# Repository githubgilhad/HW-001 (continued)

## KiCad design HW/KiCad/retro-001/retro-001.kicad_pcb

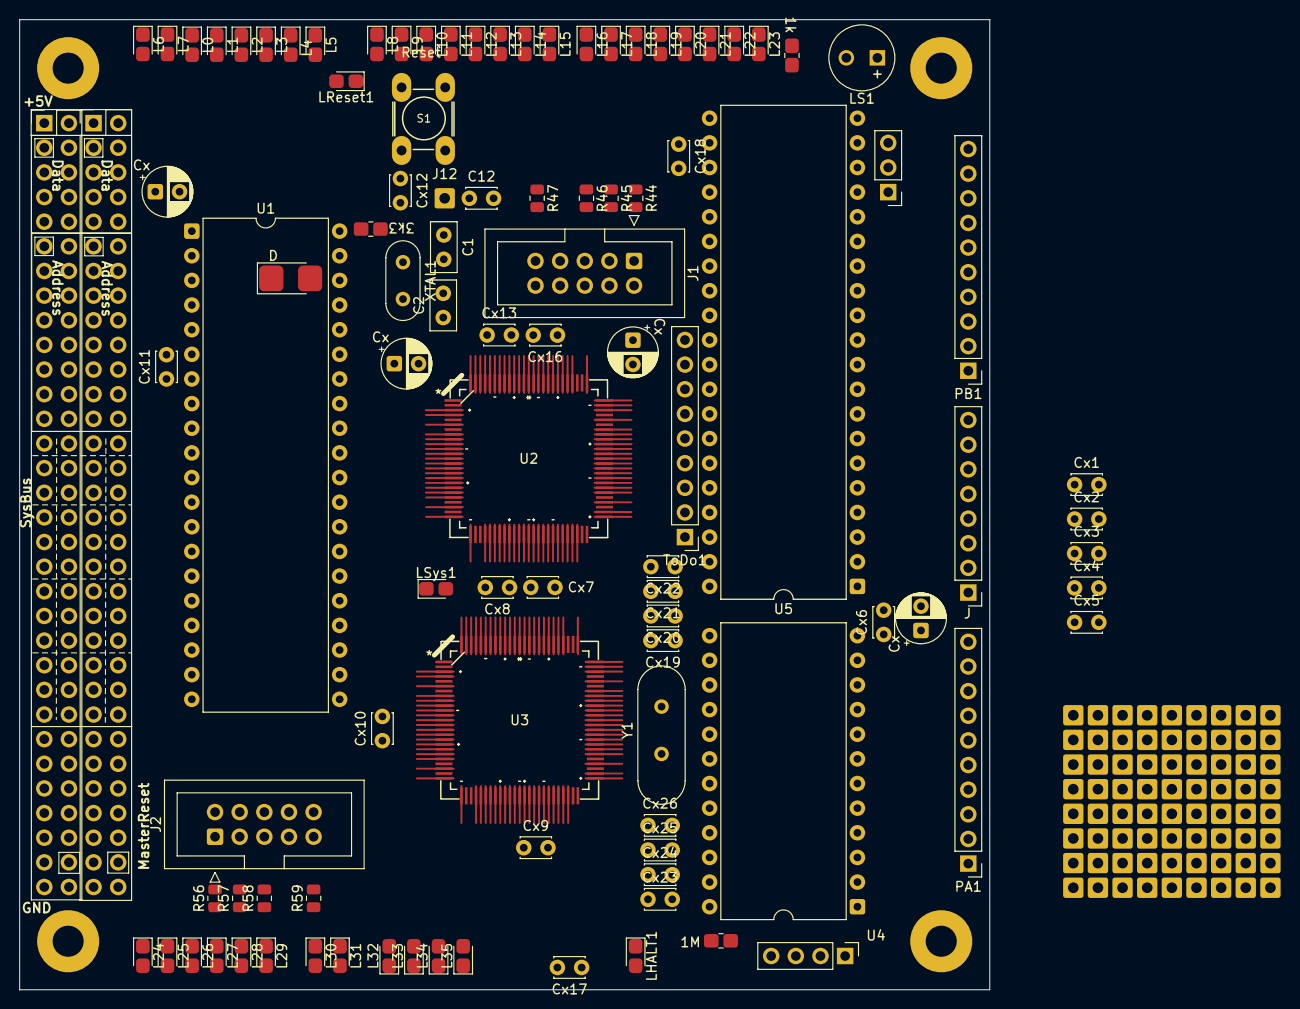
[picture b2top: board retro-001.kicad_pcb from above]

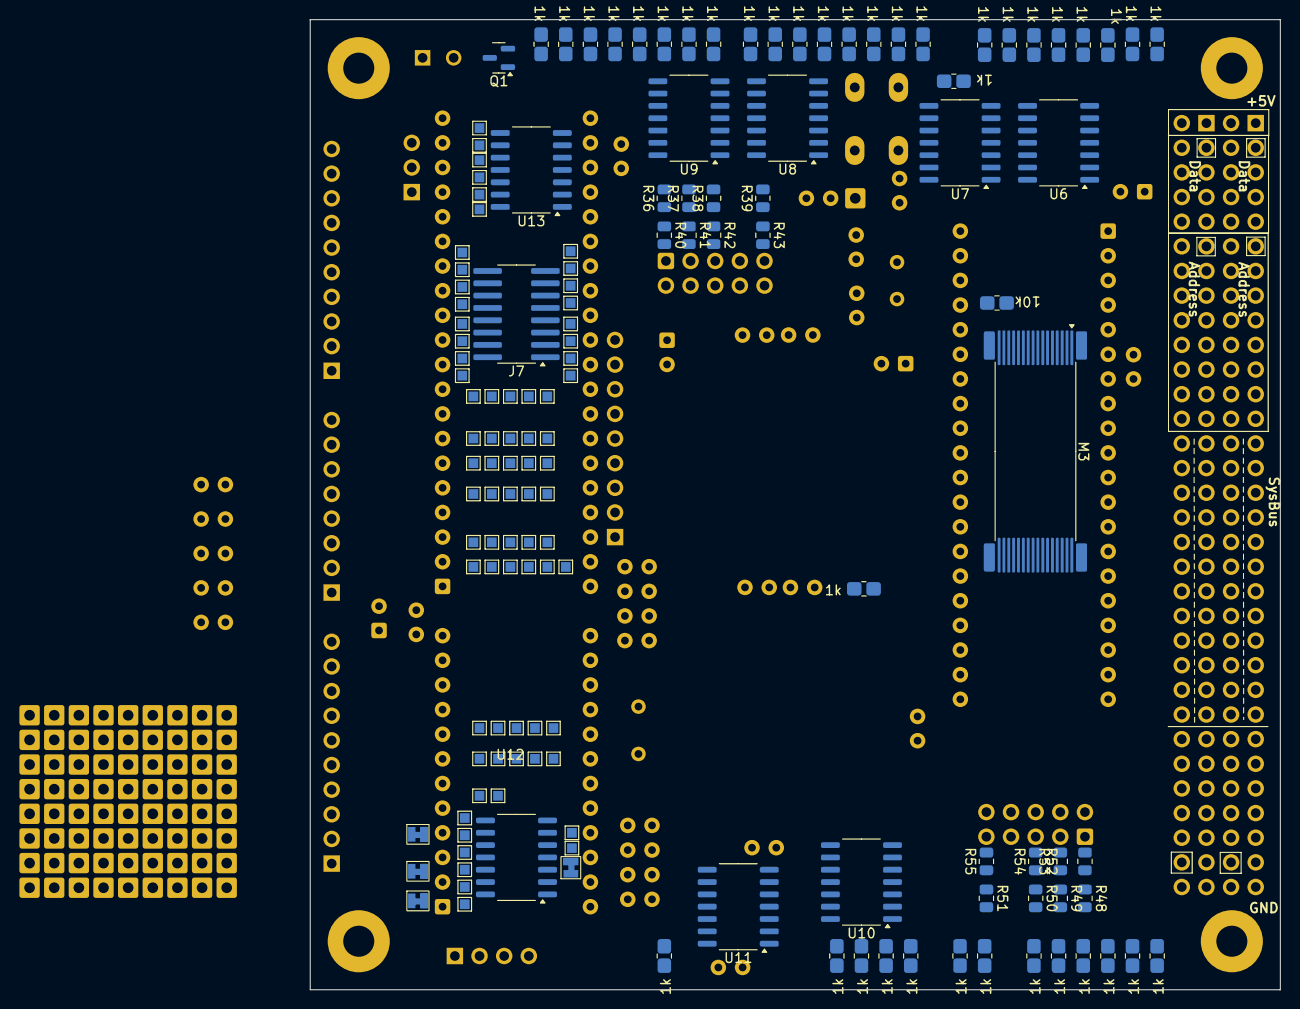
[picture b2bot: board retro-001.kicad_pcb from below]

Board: 2 copper layers, 100.0 x 100.0 mm, 322 parts (144 on the bottom side), 280 nets, no tracks yet.

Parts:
C1, C2: 20p; C_Disc_D5.0mm_W2.5mm_P2.50mm
C12: 100n RESET; C_Disc_D3.0mm_W2.0mm_P2.50mm
Cx1, Cx2, Cx3, Cx4, Cx5, Cx6, Cx7, Cx8, Cx9, Cx10, Cx11, Cx12, Cx13, Cx16, Cx17, Cx18: Cx; C_Disc_D3.0mm_W2.0mm_P2.50mm
Cx14, Cx15, Cx27, Cx28: Cx; CP_Radial_D5.0mm_P2.50mm
Cx19, Cx20, Cx21, Cx22, Cx23, Cx24, Cx25, Cx26: 10p; C_Disc_D3.0mm_W2.0mm_P2.50mm
D2: D; D_1210_3225Metric_HandSolder
H5, H6, H7, H8: MountingHole; MountingHole_3.2mm_M3_Pad
J1, J2: Conn_02x05_JTAG; IDC-Header_2x05_P2.54mm_Vertical
J3: Serial; PinHeader_1x04_P2.54mm_Vertical
J4: SysBus; PinSocket_2x32_P2.54mm_Vertical
J6: SysBus; PinHeader_2x32_P2.54mm_Vertical_down
J7: Conn_01x16_Pin; G_SOIC-16_3.9x9.9mm_HandSolder
J12: Reset; PinHole_1x01_2.54xrectangle
J21, J22, J37, J38, J39, J40, J41, J42, J43, J44, J45, J46, J47, J48, J49, J50, J51, J52, J53, J54, J55, J56, J57, J58, J59, J60, J61, J62, J63, J64, J65, J66, J67, J68, J69, J70, J71, J72, J73, J74, J75, J76, J77, J78, J79, J80, J81, J82, J83, J84, J85, J86, J87, J88, J89, J90, J91, J92, J93, J94, J95, J96, J97, J98, J99, J100, J101, J102, J103, J104, J105, J106: x; PinHole_1x01_2.54xrectangle
JP1: Nx4; SolderJumper-2_P1.3mm_Bridged_Pad1.0x1.5mm
JP2: Nx5; SolderJumper-2_P1.3mm_Bridged_Pad1.0x1.5mm
JP3: Nx6; SolderJumper-2_P1.3mm_Bridged_Pad1.0x1.5mm
JP13: Nx3; SolderJumper-2_P1.3mm_Bridged_Pad1.0x1.5mm
Jx1: BugFix; PinHeader_1x03_P2.54mm_Vertical
Jx4: J; PinHeader_1x08_P2.54mm_Vertical
L0, L1, L2, L3, L4, L5, L6, L7, L8, L9, L10, L11, L12, L13, L14, L15, L16, L17, L18, L19, L20, L21, L22, L23, L24, L25, L26, L27, L28, L29, L30, L31, L32, L33, L34, L35: A0; LED_0805_2012Metric
LHALT1: A0; LED_0805_2012Metric
LReset1: A0; LED_0805_2012Metric
LS1: Speaker_Crystal; MagneticBuzzer_Kingstate_KCG0601
LSys1: A0; LED_0805_2012Metric
M3: CY7C109D-10ZXI; G_TSOP-I-32_18.4x8mm_HandSolder
PA1: J; PinHeader_1x10_P2.54mm_Vertical
PB1: J; PinHeader_1x10_P2.54mm_Vertical
Q1: MMBT3904; SOT-23
R0, R1, R2, R3, R4, R5, R6, R7, R8, R9, R10, R11, R12, R13, R14, R15, R16, R17, R18, R19, R20, R21, R22, R23, R24, R25, R26, R27, R28, R29, R30, R31, R32, R33, R34, R35, R61, R62, R65, R66: 1k; R_0805_2012Metric_Pad1.20x1.40mm_HandSolder
R36, R37, R38, R39, R44, R45, R46, R47, R48, R49, R50, R51, R56, R57, R58, R59: 5k8; R_0805_2012Metric
R40, R41, R42, R43, R52, R53, R54, R55: 220; R_0805_2012Metric
R60: 1M; R_0805_2012Metric_Pad1.20x1.40mm_HandSolder
R63: 3k3; R_0805_2012Metric_Pad1.20x1.40mm_HandSolder
R64: 10k; R_0805_2012Metric_Pad1.20x1.40mm_HandSolder
S1: Reset; G_Arduino_switch
TP1, TP16: 7; TestPoint_Pad_1.0x1.0mm
TP2, TP9: 0; TestPoint_Pad_1.0x1.0mm
TP3, TP10: 1; TestPoint_Pad_1.0x1.0mm
TP4, TP11: 2; TestPoint_Pad_1.0x1.0mm
TP5, TP12: 3; TestPoint_Pad_1.0x1.0mm
TP6, TP13: 4; TestPoint_Pad_1.0x1.0mm
TP7, TP14: 5; TestPoint_Pad_1.0x1.0mm
TP8, TP15: 6; TestPoint_Pad_1.0x1.0mm
TP17: D; TestPoint_Pad_1.0x1.0mm
TP18: Clk; TestPoint_Pad_1.0x1.0mm
TP19: Q; TestPoint_Pad_1.0x1.0mm
TP20: ~{Q}; TestPoint_Pad_1.0x1.0mm
TP21: ~{R}; TestPoint_Pad_1.0x1.0mm
TP22: ~{S}; TestPoint_Pad_1.0x1.0mm
TP23: N3; TestPoint_Pad_1.0x1.0mm
TP24: N4; TestPoint_Pad_1.0x1.0mm
TP25: N5; TestPoint_Pad_1.0x1.0mm
TP26: N6; TestPoint_Pad_1.0x1.0mm
TP27: ~{N3}; TestPoint_Pad_1.0x1.0mm
TP28: ~{N4}; TestPoint_Pad_1.0x1.0mm
TP29: ~{N5}; TestPoint_Pad_1.0x1.0mm
TP30: ~{N6}; TestPoint_Pad_1.0x1.0mm
TP31, TP32, TP33, TP34, TP35, TP36, TP37, TP38, TP39, TP40, TP41, TP42, TP43, TP44, TP45, TP46, TP47, TP48, TP49, TP50, TP51, TP52, TP53, TP54, TP55, TP56, TP57, TP58, TP59, TP60, TP61, TP62, TP63: IO; TestPoint_Pad_1.0x1.0mm
TP65, TP66, TP67, TP68, TP69, TP70, TP71, TP72, TP73, TP74: I; TestPoint_Pad_1.0x1.0mm
ToDo1: J; PinHeader_1x09_P2.54mm_Vertical
U1: HD6309; DIP-40_W15.24mm
U2, U3: ATF1504AS-10AU100; ATF1504-AS_TQFP100_long
U4: MC68B50; DIP-24_W15.24mm
U5: 6822; DIP-40_W15.24mm
U6, U7, U8, U9, U10, U11: 74HC14; SOIC-14_3.9x8.7mm_P1.27mm
U12: 74HC04; SOIC-14_3.9x8.7mm_P1.27mm
U13: 74HC74; SOIC-14_3.9x8.7mm_P1.27mm
XTAL1: 16MHz; Crystal_HC52-6mm_Vertical
Y1: 1.8432 MHz; Crystal_THT_15_5mm

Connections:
+5V: Cx1.1, Cx2.1, Cx3.1, Cx4.1, Cx5.1, Cx6.1, Cx7.1, Cx8.1, Cx9.1, Cx10.1, Cx11.1, Cx12.1, Cx13.1, Cx14.1, Cx15.1, Cx16.1, Cx17.1, Cx18.1, Cx27.1, Cx28.1, D2.1 (K), J1.4 (Vcc), J2.4 (Vcc), J3.4, J4.1, J4.2, J6.1, J6.2, Jx4.8, L0.2 (A), L1.2 (A), L2.2 (A), L3.2 (A), L4.2 (A), L5.2 (A), L6.2 (A), L7.2 (A), L8.2 (A), L9.2 (A), L10.2 (A), L11.2 (A), L12.2 (A), L13.2 (A), L14.2 (A), L15.2 (A), L16.2 (A), L17.2 (A), L18.2 (A), L19.2 (A), L20.2 (A), L21.2 (A), L22.2 (A), L23.2 (A), L32.2 (A), L33.2 (A), L34.2 (A), L35.2 (A), LS1.1, M3.6 (CS2/CE2), M3.8 (VCC), PA1.10, PB1.10, R36.2, R37.2, R38.2, R39.2, R48.2, R49.2, R50.2, R51.2, R62.2, R63.1, R64.1, R65.2, R66.2, U1.7 (VCC), U2.3 (VCCIO), U2.18 (VCCIO), U2.34 (VCCIO), U2.39 (VCCINT), U2.51 (VCCIO), U2.66 (VCCIO), U2.82 (VCCIO), U2.91 (VCCINT), U3.3 (VCCIO), U3.18 (VCCIO), U3.34 (VCCIO), U3.39 (VCCINT), U3.51 (VCCIO), U3.66 (VCCIO), U3.82 (VCCIO), U3.91 (VCCINT), U4.8 (CS0), U4.10 (CS1), U4.12 (VCC), U5.20 (VCC), U5.22 (CS0), U5.24 (CS1), U6.14 (VCC), U7.14 (VCC), U8.14 (VCC), U9.14 (VCC), U10.14 (VCC), U11.14 (VCC), U12.14 (VCC), U13.1 (~R), U13.4 (~S), U13.14 (VCC)
/A12: J4.23, J6.23, M3.12 (A12), U3.100 (I/O)
/A13: J4.24, J6.24, M3.4 (A13), U3.99 (I/O)
/A14: J4.25, J6.25, M3.11 (A14), U3.98 (I/O)
/A15: J4.26, J6.26, M3.7 (A15), U3.97 (I/O)
/CA0: J4.11, J6.11, M3.20 (A0), U1.8 (A0), U2.6 (I/O), U4.11 (RS), U5.36 (RS0), U7.5
/CA1: J4.12, J6.12, M3.19 (A1), U1.9 (A1), U2.8 (I/O), U5.35 (RS1), U7.9
/CA2: J4.13, J6.13, M3.18 (A2), U1.10 (A2), U2.9 (I/O), U7.11
/CA3: J4.14, J6.14, M3.17 (A3), U1.11 (A3), U2.10 (I/O), U7.13
/CA4: J4.15, J6.15, M3.16 (A4), U1.12 (A4), U2.12 (I/O/PD1), U8.1
/CA5: J4.16, J6.16, M3.15 (A5), U1.13 (A5), U2.13 (I/O), U8.3
/CA6: J4.17, J6.17, M3.14 (A6), U1.14 (A6), U2.14 (I/O), U8.5
/CA7: J4.18, J6.18, M3.13 (A7), U1.15 (A7), U2.16 (I/O), U8.9
/CA8: J4.19, J6.19, M3.3 (A8), U1.16 (A8), U2.17 (I/O), U8.11
/CA9: J4.20, J6.20, M3.2 (A9), U1.17 (A9), U2.19 (I/O), U8.13
/CA10: J4.21, J6.21, M3.31 (A10), U1.18 (A10), U2.20 (I/O), U9.1
/CA11: J4.22, J6.22, M3.1 (A11), U1.19 (A11), U2.21 (I/O), U9.3
/E: J4.61, J6.61, U1.34 (E), U2.31 (I/O), U3.17 (I/O), U4.14 (E), U5.25 (ENABLE), U13.3 (C)
/Rx: J3.1, U4.2 (Rx_Data)
/Tx: J3.2, U4.6 (Tx_Data)
/mA_16: J4.27, J6.27, U3.69 (I/O)
/mA_HALT: J4.29, J6.29, U3.68 (I/O)
/mA_READ: J4.31, J6.31, U3.67 (I/O)
/mA_SHARE_DIRTY: J4.33, J6.33, U3.65 (I/O)
/mA_SHARE_GRANTED: J4.35, J6.35, U3.64 (I/O)
/mA_SHARE_REQUEST: J4.37, J6.37, U3.63 (I/O)
/mA_SHARE_SELECT: J4.51, J6.51, U3.52 (I/O)
/mB_16: J4.28, J6.28, U3.32 (I/O)
/mB_HALT: J4.30, J6.30, U3.33 (I/O)
/mB_READ: J4.32, J6.32, U3.35 (I/O)
/mB_SHARE_DIRTY: J4.34, J6.34, U3.36 (I/O)
/mB_SHARE_GRANTED: J4.36, J6.36, U3.37 (I/O)
/mB_SHARE_REQUEST: J4.38, J6.38, U3.40 (I/O)
/mB_SHARE_SELECT: J4.52, J6.52, U3.48 (I/O)
/vCA1: Jx4.1, U5.40 (CA1)
/vCA2: Jx4.2, U5.39 (CA2)
/vCB1: Jx1.1, Jx4.3, U13.2 (D)
/vCB2: Jx4.4, U5.19 (CB2)
/v~IRQA: Jx4.5, U5.38 (~IRQA)
/v~IRQB: Jx4.6, U5.37 (~IRQB)
/~Dev_Sel_3: J4.58, J6.58, U2.83 (I/O), U10.9
/~Dev_Sel_4: J4.59, J6.59, U2.81 (I/O), U10.11
/~Dev_Sel_5: J4.60, J6.60, U2.80 (I/O), U10.13
/~FIRQ: J4.57, J6.57, U1.4 (~FIRQ)
/~IRQ: J4.56, J6.56, U1.3 (~IRQ), U4.7 (~IRQ)
/~NMI: J4.55, J6.55, U1.2 (~NMI)
/~Read: J4.54, J6.54, M3.32 (~OE), U2.96 (I/O), U11.1
/~Write: J4.53, J6.53, M3.5 (~WE), U2.94 (I/O), U11.3
ACIA Clk 1.8432 MHz: U4.3 (Rx_CLK), U4.4 (Tx_CLK), U12.4
A_G_A_DIR: J4.47, J6.47, U3.56 (I/O)
A_G_D_DIR: J4.49, J6.49, U3.54 (I/O)
A_G_ENABLE: J4.45, J6.45, U3.57 (I/O)
A_S_READ: J4.41, J6.41, U3.60 (I/O)
A_S_SELECT: J4.39, J6.39, U3.61 (I/O)
A_S_WRITE: J4.43, J6.43, U3.58 (I/O)
BA: ToDo1.6, U1.6 (BA)
BS: ToDo1.5, U1.5 (BS)
B_G_A_DIR: J4.48, J6.48, U3.46 (I/O)
B_G_D_DIR: J4.50, J6.50, U3.47 (I/O)
B_G_ENABLE: J4.46, J6.46, U3.45 (I/O)
B_S_READ: J4.42, J6.42, U3.42 (I/O/PD2)
B_S_SELECT: J4.40, J6.40, U3.41 (I/O)
B_S_WRITE: J4.44, J6.44, U3.44 (I/O)
CA12: U1.20 (A12), U2.23 (I/O), U3.23 (I/O), U9.5
CA13: U1.21 (A13), U2.25 (I/O), U3.25 (I/O), U9.9
CA14: U1.22 (A14), U2.29 (I/O), U3.29 (I/O), U9.11
CA15: U1.23 (A15), U2.30 (I/O), U3.30 (I/O), U9.13
D0: J4.3, J6.3, M3.21 (DQ0), U1.31 (D0), U3.6 (I/O), U4.22 (D0), U5.33 (D0), U7.1
D1: J4.4, J6.4, M3.22 (DQ1), U1.30 (D1), U3.8 (I/O), U4.21 (D1), U5.32 (D1), U7.3
D2: J4.5, J6.5, M3.23 (DQ2), U1.29 (D2), U3.9 (I/O), U4.20 (D2), U5.31 (D2), U6.1
D3: J4.6, J6.6, M3.25 (DQ3), U1.28 (D3), U3.10 (I/O), U4.19 (D3), U5.30 (D3), U6.3
D4: J4.7, J6.7, M3.26 (DQ4), U1.27 (D4), U3.12 (I/O/PD1), U4.18 (D4), U5.29 (D4), U6.5
D5: J4.8, J6.8, M3.27 (DQ5), U1.26 (D5), U3.13 (I/O), U4.17 (D5), U5.28 (D5), U6.9
D6: J4.9, J6.9, M3.28 (DQ6), U1.25 (D6), U3.14 (I/O), U4.16 (D6), U5.27 (D6), U6.11
D7: J4.10, J6.10, M3.29 (DQ7), U1.24 (D7), U3.16 (I/O), U4.15 (D7), U5.26 (D7), U6.13
GA16: M3.10 (A16), U3.96 (I/O)
GND: C1.1, C2.1, C12.2, Cx1.2, Cx2.2, Cx3.2, Cx4.2, Cx5.2, Cx6.2, Cx7.2, Cx8.2, Cx9.2, Cx10.2, Cx11.2, Cx12.2, Cx13.2, Cx14.2, Cx15.2, Cx16.2, Cx17.2, Cx18.2, Cx19.2, Cx20.2, Cx21.2, Cx22.2, Cx23.2, Cx24.2, Cx25.2, Cx26.2, Cx27.2, Cx28.2, J1.2 (GND), J1.10 (GND), J2.2 (GND), J2.10 (GND), J3.3, J4.63, J4.64, J6.63, J6.64, JP1.1 (A), JP2.1 (A), JP3.1 (A), JP13.1 (A), Jx4.7, L24.1 (K), L25.1 (K), L26.1 (K), L27.1 (K), L28.1 (K), L29.1 (K), L30.1 (K), L31.1 (K), LSys1.1 (K), M3.24 (GND), PA1.9, PB1.9, Q1.2 (E), R44.1, R45.1, R46.1, R47.1, R56.1, R57.1, R58.1, R59.1, S1.3 (K), S1.4 (A), ToDo1.9, U1.1 (VSS), U2.11 (GND), U2.26 (GND), U2.38 (GND), U2.43 (GND), U2.59 (GND), U2.74 (GND), U2.86 (GND), U2.95 (GND), U3.11 (GND), U3.26 (GND), U3.38 (GND), U3.43 (GND), U3.59 (GND), U3.74 (GND), U3.86 (GND), U3.95 (GND), U4.1 (VSS), U4.23 (~DCD), U4.24 (~CTS), U5.1 (VSS), U6.7 (GND), U7.7 (GND), U8.7 (GND), U9.7 (GND), U10.7 (GND), U11.7 (GND), U12.7 (GND), U13.7 (GND)
JT2_TCK: R48.1, R52.1, R56.2, U3.62 (I/O/TCK)
JT2_TDI: R51.1, R55.1, R59.2, U3.4 (I/O/TDI)
JT2_TDO: R49.1, R53.1, R57.2, U3.73 (I/O/TDO)
JT2_TMS: R50.1, R54.1, R58.2, U3.15 (I/O/TMS)
JT_TCK: R36.1, R40.1, R44.2, U2.62 (I/O/TCK)
JT_TDI: R39.1, R43.1, R47.2, U2.4 (I/O/TDI)
JT_TDO: R37.1, R41.1, R45.2, U2.73 (I/O/TDO)
JT_TMS: R38.1, R42.1, R46.2, U2.15 (I/O/TMS)
MR0: U2.100 (I/O), U3.94 (I/O), U11.5
MR1: U2.99 (I/O), U3.93 (I/O), U11.9
MR2: U2.98 (I/O), U3.92 (I/O), U11.11
MR3: U2.97 (I/O), U3.84 (I/O), U11.13
MRDY: ToDo1.7, U1.36 (MRDY)
MasterReset: C12.1, D2.2 (A), J4.62, J6.62, J12.1, LReset1.1 (K), R64.2, S1.1, S1.2, U1.37 (~RESET), U2.33 (I/O), U3.20 (I/O), U5.34 (~RESET)
unnamed: Cx19.1, Cx20.1, Cx21.1, Cx22.1, R60.1, U12.2, U12.3, Y1.2
unnamed: Cx23.1, Cx24.1, Cx25.1, Cx26.1, R60.2, U12.1, Y1.1
unnamed: J1.1 (TCK), R40.2
unnamed: J1.9 (TDI), R43.2
unnamed: J1.3 (TDO), R41.2
unnamed: J1.5 (TMS), R42.2
unnamed: J2.1 (TCK), R52.2
unnamed: J2.9 (TDI), R55.2
unnamed: J2.3 (TDO), R53.2
unnamed: J2.5 (TMS), R54.2
unnamed: J7.1, TP2.1
unnamed: J7.2, TP3.1
unnamed: J7.3, TP4.1
unnamed: J7.4, TP5.1
unnamed: J7.5, TP6.1
unnamed: J7.6, TP7.1
unnamed: J7.7, TP8.1
unnamed: J7.8, TP1.1
unnamed: J7.9, TP16.1
unnamed: J7.10, TP15.1
unnamed: J7.11, TP14.1
unnamed: J7.12, TP13.1
unnamed: J7.13, TP12.1
unnamed: J7.14, TP11.1
unnamed: J7.15, TP10.1
unnamed: J7.16, TP9.1
unnamed: JP1.2 (B), TP24.1, U12.9
unnamed: JP2.2 (B), TP25.1, U12.11
unnamed: JP3.2 (B), TP26.1, U12.13
unnamed: JP13.2 (B), TP23.1, U12.5
unnamed: Jx1.2, U5.18 (CB1)
unnamed: Jx1.3, U13.5 (Q)
unnamed: L0.1 (K), R0.1
unnamed: L1.1 (K), R1.1
unnamed: L2.1 (K), R2.1
unnamed: L3.1 (K), R3.1
unnamed: L4.1 (K), R4.1
unnamed: L5.1 (K), R5.1
unnamed: L6.1 (K), R6.1
unnamed: L7.1 (K), R7.1
unnamed: L8.1 (K), R8.1
unnamed: L9.1 (K), R9.1
unnamed: L10.1 (K), R10.1
unnamed: L11.1 (K), R11.1
unnamed: L12.1 (K), R12.1
unnamed: L13.1 (K), R13.1
unnamed: L14.1 (K), R14.1
unnamed: L15.1 (K), R15.1
unnamed: L16.1 (K), R16.1
unnamed: L17.1 (K), R17.1
unnamed: L18.1 (K), R18.1
unnamed: L19.1 (K), R19.1
unnamed: L20.1 (K), R20.1
unnamed: L21.1 (K), R21.1
unnamed: L22.1 (K), R22.1
unnamed: L23.1 (K), R23.1
unnamed: L24.2 (A), R24.1
unnamed: L25.2 (A), R25.1
unnamed: L26.2 (A), R26.1
unnamed: L27.2 (A), R27.1
unnamed: L28.2 (A), R28.1
unnamed: L29.2 (A), R29.1
unnamed: L30.2 (A), R30.1
unnamed: L31.2 (A), R31.1
unnamed: L32.1 (K), R32.1
unnamed: L33.1 (K), R33.1
unnamed: L34.1 (K), R34.1
unnamed: L35.1 (K), R35.1
unnamed: LHALT1.2 (A), R65.1
unnamed: LReset1.2 (A), R66.1
unnamed: LSys1.2 (A), R62.1
unnamed: PA1.1, U5.2 (PA0)
unnamed: PA1.2, U5.3 (PA1)
unnamed: PA1.3, U5.4 (PA2)
unnamed: PA1.4, U5.5 (PA3)
unnamed: PA1.5, U5.6 (PA4)
unnamed: PA1.6, U5.7 (PA5)
unnamed: PA1.7, U5.8 (PA6)
unnamed: PA1.8, U5.9 (PA7)
unnamed: PB1.1, U5.10 (PB0)
unnamed: PB1.2, U5.11 (PB1)
unnamed: PB1.3, U5.12 (PB2)
unnamed: PB1.4, U5.13 (PB3)
unnamed: PB1.5, U5.14 (PB4)
unnamed: PB1.6, U5.15 (PB5)
unnamed: PB1.7, U5.16 (PB6)
unnamed: PB1.8, R61.1, U5.17 (PB7)
unnamed: Q1.1 (B), R61.2
unnamed: LS1.2, Q1.3 (C)
unnamed: R0.2, U6.2
unnamed: R1.2, U6.4
unnamed: R2.2, U6.6
unnamed: R3.2, U6.8
unnamed: R4.2, U6.10
unnamed: R5.2, U6.12
unnamed: R6.2, U7.2
unnamed: R7.2, U7.4
unnamed: R8.2, U7.6
unnamed: R9.2, U7.8
unnamed: R10.2, U7.10
unnamed: R11.2, U7.12
unnamed: R12.2, U8.2
unnamed: R13.2, U8.4
unnamed: R14.2, U8.6
unnamed: R15.2, U8.8
unnamed: R16.2, U8.10
unnamed: R17.2, U8.12
unnamed: R18.2, U9.2
unnamed: R19.2, U9.4
unnamed: R20.2, U9.6
unnamed: R21.2, U9.8
unnamed: R22.2, U9.10
unnamed: R23.2, U9.12
unnamed: R24.2, U10.2
unnamed: R25.2, U10.4
unnamed: R26.2, U10.6
unnamed: R27.2, U10.8
unnamed: R28.2, U10.10
unnamed: R29.2, U10.12
unnamed: R30.2, U11.2
unnamed: R31.2, U11.4
unnamed: R32.2, U11.6
unnamed: R33.2, U11.8
unnamed: R34.2, U11.10
unnamed: R35.2, U11.12
unnamed: TP27.1, U12.6
unnamed: TP28.1, U12.8
unnamed: TP29.1, U12.10
unnamed: TP30.1, U12.12
unnamed: TP31.1, U3.83 (I/O)
unnamed: TP32.1, U3.81 (I/O)
unnamed: TP33.1, U3.80 (I/O)
unnamed: TP34.1, U3.79 (I/O)
unnamed: TP35.1, U3.76 (I/O)
unnamed: TP36.1, U3.75 (I/O)
unnamed: TP37.1, U3.71 (I/O)
unnamed: TP38.1, U2.75 (I/O)
unnamed: TP39.1, U2.71 (I/O)
unnamed: TP40.1, U2.69 (I/O)
unnamed: TP41.1, U2.68 (I/O)
unnamed: TP42.1, U2.67 (I/O)
unnamed: TP43.1, U2.65 (I/O)
unnamed: TP44.1, U2.64 (I/O)
unnamed: TP45.1, U2.63 (I/O)
unnamed: TP46.1, U2.61 (I/O)
unnamed: TP47.1, U2.60 (I/O)
unnamed: TP48.1, U2.58 (I/O)
unnamed: TP49.1, U2.57 (I/O)
unnamed: TP50.1, U2.56 (I/O)
unnamed: TP51.1, U2.54 (I/O)
unnamed: TP52.1, U2.52 (I/O)
unnamed: TP53.1, U2.48 (I/O)
unnamed: TP54.1, U2.47 (I/O)
unnamed: TP55.1, U2.46 (I/O)
unnamed: TP56.1, U2.45 (I/O)
unnamed: TP57.1, U2.44 (I/O)
unnamed: TP59.1, U2.41 (I/O)
unnamed: TP60.1, U2.40 (I/O)
unnamed: TP61.1, U2.37 (I/O)
unnamed: TP62.1, U2.36 (I/O)
unnamed: TP63.1, U2.35 (I/O)
unnamed: C2.2, U1.38 (EXTAL), XTAL1.2
unnamed: C1.2, U1.39 (XTAL), XTAL1.1
unnamed: TP67.1, U2.88 (12V/INPUT/OE1)
unnamed: TP68.1, U2.87 (INPUT/GCLK1)
unnamed: TP66.1, U2.89 (INPUT/GCLR)
unnamed: TP65.1, U2.90 (INPUT/OE2/GCLK2)
unnamed: TP69.1, U2.85 (I/O/GCLK3)
unnamed: TP58.1, U2.42 (I/O/PD2)
unnamed: TP72.1, U3.88 (12V/INPUT/OE1)
unnamed: TP73.1, U3.87 (INPUT/GCLK1)
unnamed: TP71.1, U3.89 (INPUT/GCLR)
unnamed: TP70.1, U3.90 (INPUT/OE2/GCLK2)
unnamed: TP74.1, U3.85 (I/O/GCLK3)
unnamed: TP18.1, U13.11 (C)
unnamed: TP17.1, U13.12 (D)
unnamed: TP19.1, U13.9 (Q)
unnamed: TP20.1, U13.8 (~Q)
unnamed: TP21.1, U13.13 (~R)
unnamed: TP22.1, U13.10 (~S)
Q: ToDo1.4, U1.35 (Q)
R~W: U1.32 (R/~W), U2.32 (I/O), U3.19 (I/O), U4.13 (R/~W), U5.21 (R/~W)
~DMA/BREQ: ToDo1.8, U1.33 (~DMA/BREQ)
~Dev_Sel_0: M3.30 (~CS1/~CE1), U2.93 (I/O), U3.31 (I/O), U10.1
~Dev_Sel_1: ToDo1.3, U2.92 (I/O), U5.23 (~CS2), U10.3
~Dev_Sel_2: U2.84 (I/O), U4.9 (CS2), U10.5
~Dev_Sel_6: ToDo1.2, U2.79 (I/O)
~Dev_Sel_7: ToDo1.1, U2.76 (I/O)
~HALT: LHALT1.1 (K), R63.2, U1.40 (~HALT), U3.21 (I/O)

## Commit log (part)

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2026-05-14 uvodni commit
2026-05-15 uvodni nacrt
2026-05-24 retro-002, mozna funkcni?
2026-05-26 nejaka zmena
2026-06-05 rozvrzeni registru
2026-06-18 Pridana EEPROM, ucesano, pridana rozpracovana PLD
2026-06-29 Prvni navrh ATF2
